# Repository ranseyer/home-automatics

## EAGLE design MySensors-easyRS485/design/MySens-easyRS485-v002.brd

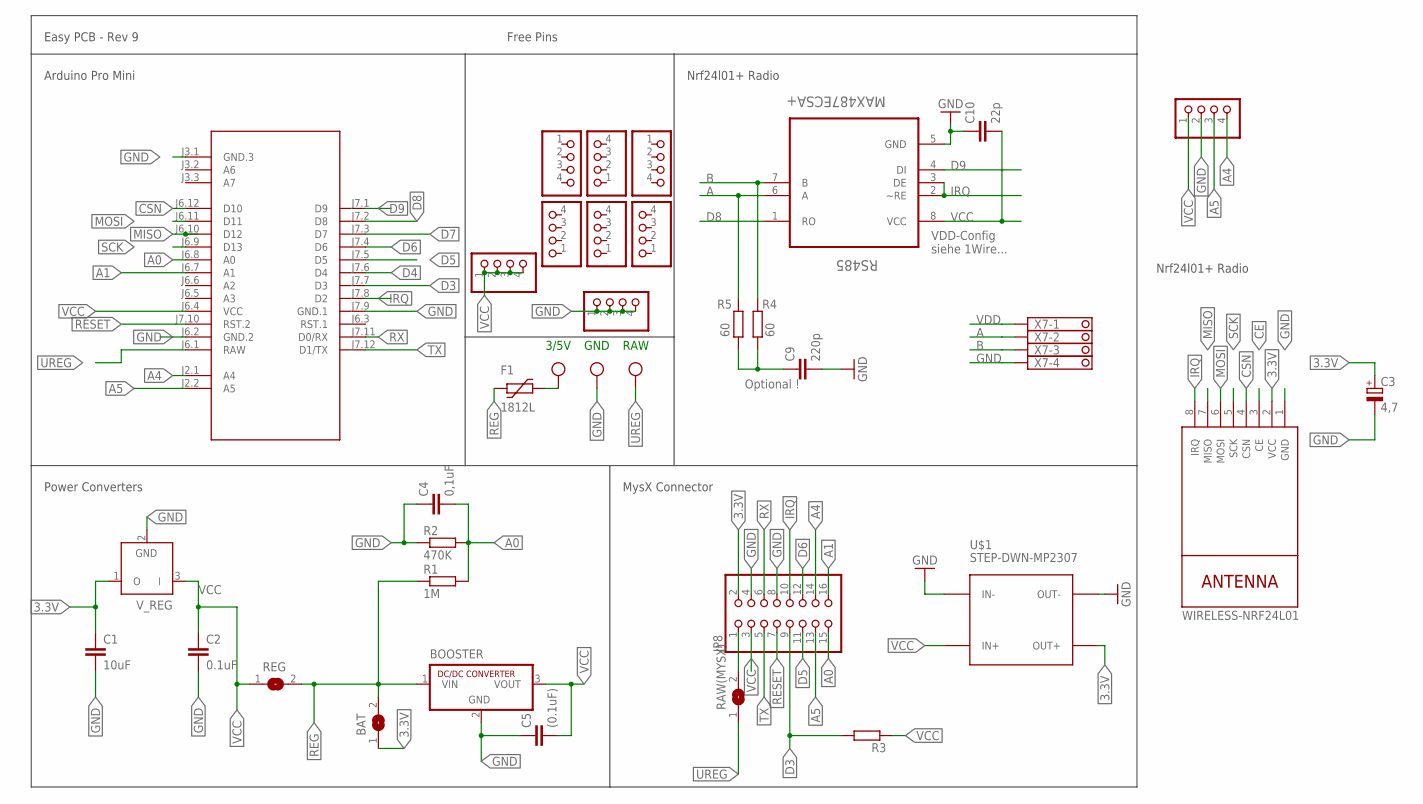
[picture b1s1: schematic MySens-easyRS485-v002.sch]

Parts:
.: W237-103
BAT: SJ
BOOSTER: R-78C1.8-1.0; SIP3
C1: 10uF; C1210
C2: 0.1uF; C1206
C3: 4,7; SMC_C
C4: 0,1uF; C1206
C5: (0.1uF); C1206
C9: 220p; C0805
C10: 22p; C0805
F1: 1812L
JP1, JP3, JP5, JP10, JP11, JP12, JP14, JP15, JP16: PINHD-1X04_2.54-S; 1X04-S
JP8: PINHD-2X08_2.54; 2X08
M1: ARDUINO-PRO-MINI-3.3V#NP; ARDUINO-PRO-MINI#NP
NRF24L01+: WIRELESS-NRF24L01
R1: 1M; R0805
R2: 470K; R0805
R3: R-EU_R0805; R0805
R4, R5: 60; R0805
RAW(MYSX): SJ
REG: SJ
RS485: MAX487ECSA+; SOIC127P600X175-8N
U$1: STEP-DWN-MP2307; DC-DC-STEP-DOWN-MP2307
V_REG: LP2950Z; TO92
X7: 1751264

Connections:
3.3V: BAT.1, C1.1, C3.+, JP8.2, NRF24L01+.2 (VCC), U$1.OUT+, V_REG.1 (O)
A: R5.2, RS485.6 (A), X7.2
A0: C4.2, JP8.15, M1.J6.8 (A0), R1.2, R2.2
A1: JP8.16, M1.J6.7 (A1)
A4: JP8.14, JP10.4, M1.J2.1 (A4)
A5: JP8.13, JP10.3, M1.J2.2 (A5)
B: R4.2, RS485.7 (B), X7.3
CE: NRF24L01+.3 (CE)
CSN: M1.J6.12 (D10), NRF24L01+.4 (CSN)
D3: JP8.9, M1.J7.7 (D3), R3.2
D4: M1.J7.6 (D4)
D5: JP8.11, M1.J7.5 (D5)
D6: JP8.12, M1.J7.4 (D6)
D7: M1.J7.3 (D7)
D8: M1.J7.2 (D8), RS485.1 (RO)
D9: M1.J7.1 (D9), RS485.4 (DI)
GND: ..2, BOOSTER.2 (GND), C1.2, C2.2, C3.-, C4.1, C5.1, C9.2, C10.1, JP1.1, JP1.2, JP1.3, JP1.4, JP8.4, JP8.8, JP10.2, M1.J3.1 (GND.3), M1.J6.2 (GND.2), M1.J7.9 (GND.1), NRF24L01+.1 (GND), R2.1, RS485.5 (GND), U$1.IN-, U$1.OUT-, V_REG.2 (GND), X7.4
IRQ: JP8.10, M1.J7.8 (D2), NRF24L01+.8 (IRQ), RS485.2 (~RE), RS485.3 (DE)
MISO: M1.J6.10 (D12), NRF24L01+.7 (MISO)
MOSI: M1.J6.11 (D11), NRF24L01+.6 (MOSI)
unnamed: JP8.1, RAW(MYSX).2
unnamed: ..3, F1.P$2 (2)
unnamed: C9.1, R4.1, R5.1
REG: BAT.2, BOOSTER.1 (VIN), F1.P$1 (1), R1.1, REG.2
RESET: JP8.7, M1.J7.10 (RST.2)
RX: JP8.6, M1.J7.11 (D0/RX)
SCK: M1.J6.9 (D13), NRF24L01+.5 (SCK)
TX: JP8.5, M1.J7.12 (D1/TX)
UREG: ..1, M1.J6.1 (RAW), RAW(MYSX).1
VCC: BOOSTER.3 (VOUT), C2.1, C5.2, C10.2, JP3.1, JP3.2, JP3.3, JP3.4, JP8.3, JP10.1, M1.J6.4 (VCC), R3.1, REG.1, RS485.8 (VCC), U$1.IN+, V_REG.3 (I)
VDD: X7.1

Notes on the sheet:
GND
3/5V
RAW
Easy PCB - Rev 9
Arduino Pro Mini
MysX Connector
Nrf24l01+ Radio
Power Converters
Free Pins
VDD-Config siehe 1Wire...
Optional !

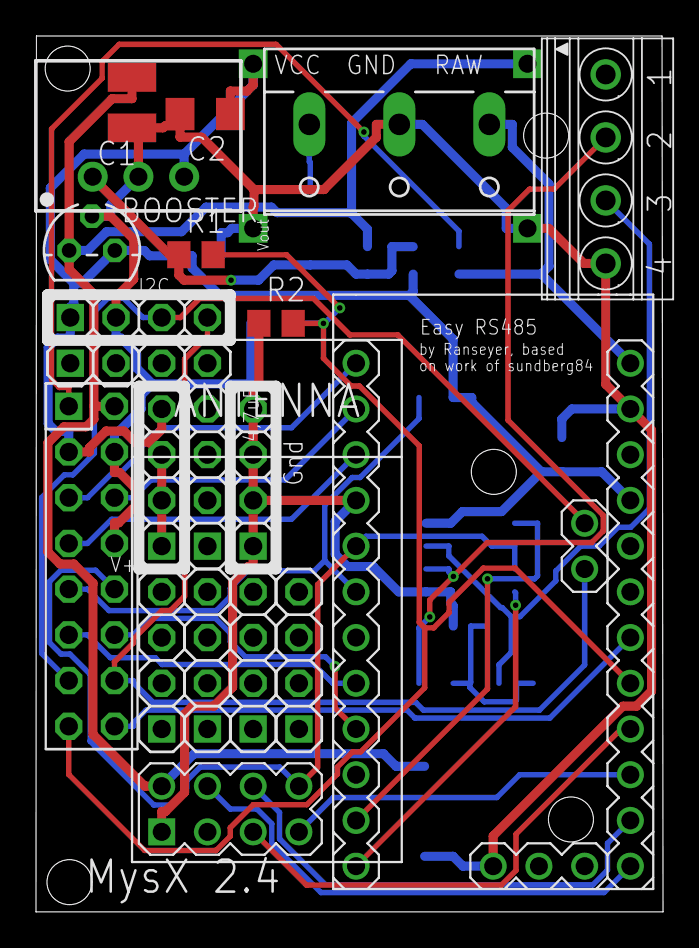
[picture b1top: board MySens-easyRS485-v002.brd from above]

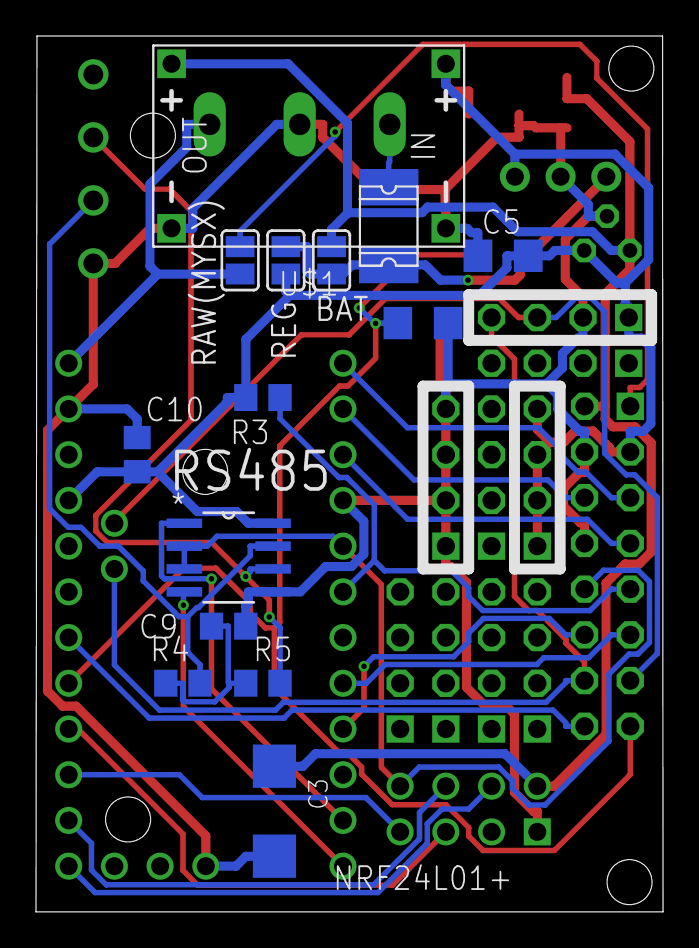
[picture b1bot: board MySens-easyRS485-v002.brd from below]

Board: 2 copper layers, 34.8 x 48.7 mm, 34 parts (14 on the bottom side), 27 nets.

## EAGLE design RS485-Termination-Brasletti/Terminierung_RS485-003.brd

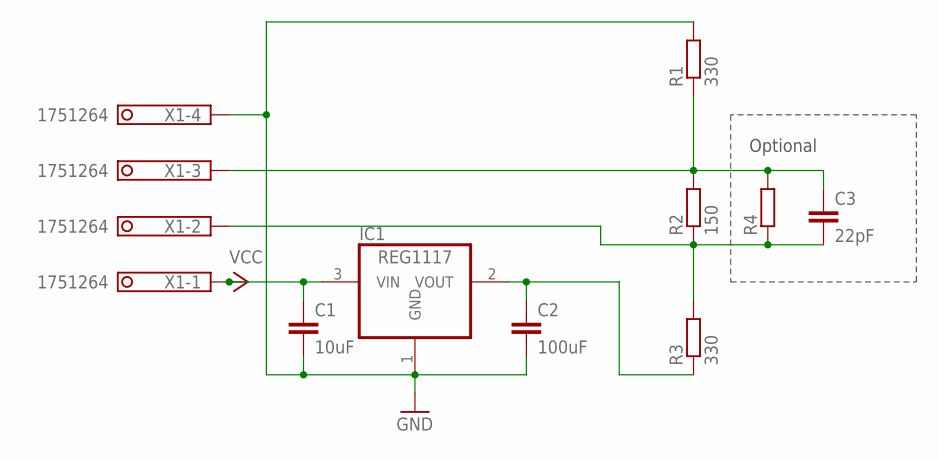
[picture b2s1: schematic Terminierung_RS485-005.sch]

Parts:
C1: 10uF; C0805K
C2: 100uF; C0805K
C3: 22pF; C0805K
IC1: REG1117; SOT223
R1, R3: 330; R0805
R2: 150; R0805
R4: R-EU_M1206; M1206
X1: 1751264

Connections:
GND: C1.2, C2.2, IC1.1 (GND), R1.2, X1.4
unnamed: C2.1, IC1.2 (VOUT), R3.1
unnamed: C3.1, R1.1, R2.2, R4.2, X1.3
unnamed: C3.2, R2.1, R3.2, R4.1, X1.2
VCC: C1.1, IC1.3 (VIN), X1.1

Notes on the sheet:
Optional

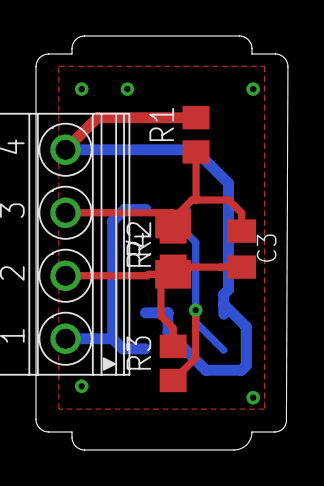
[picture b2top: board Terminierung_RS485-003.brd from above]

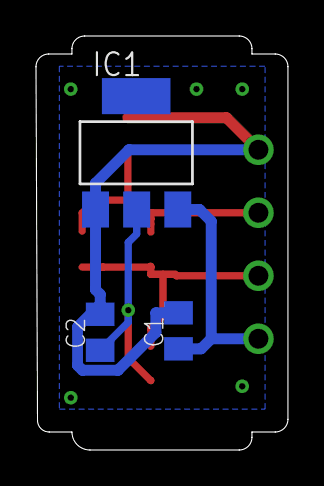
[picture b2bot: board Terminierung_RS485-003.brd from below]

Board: 2 copper layers, 14.0 x 23.0 mm, 9 parts (3 on the bottom side), 5 nets.

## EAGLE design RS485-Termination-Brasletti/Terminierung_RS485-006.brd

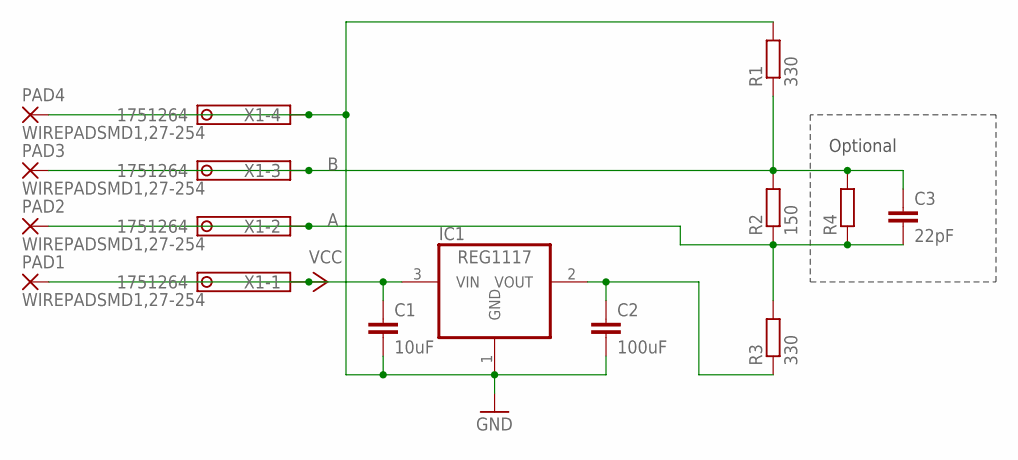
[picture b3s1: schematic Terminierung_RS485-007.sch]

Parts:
C1: 10uF; C0805K
C2: 100uF; C0805K
C3: 22pF; C0805K
IC1: REG1117; SOT223
PAD1, PAD2, PAD3, PAD4: WIREPADSMD1,27-254; SMD1,27-2,54
R1, R3: 330; R0805
R2: 150; R0805
R4: R-EU_M1206; M1206
X1: 1751264

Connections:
A: C3.2, PAD2.1, R2.1, R3.2, R4.1, X1.2
B: C3.1, PAD3.1, R1.1, R2.2, R4.2, X1.3
GND: C1.2, C2.2, IC1.1 (GND), PAD4.1, R1.2, X1.4
unnamed: C2.1, IC1.2 (VOUT), R3.1
VCC: C1.1, IC1.3 (VIN), PAD1.1, X1.1

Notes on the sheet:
Optional

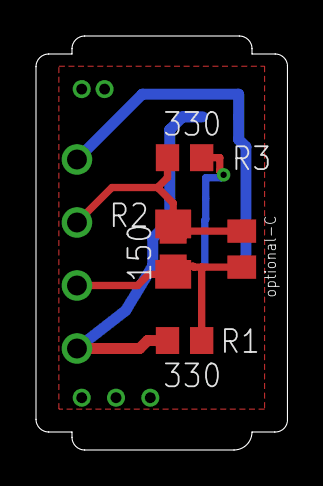
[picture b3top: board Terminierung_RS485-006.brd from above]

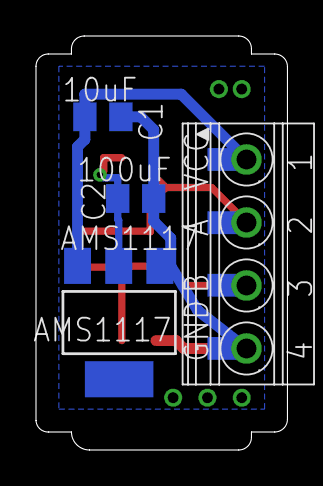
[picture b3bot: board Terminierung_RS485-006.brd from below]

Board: 2 copper layers, 14.0 x 23.0 mm, 13 parts (8 on the bottom side), 5 nets.

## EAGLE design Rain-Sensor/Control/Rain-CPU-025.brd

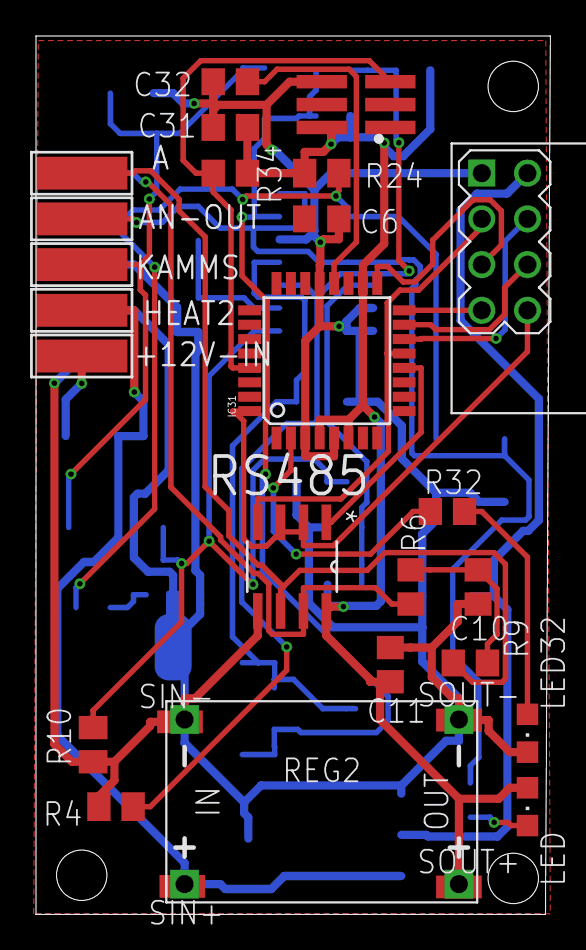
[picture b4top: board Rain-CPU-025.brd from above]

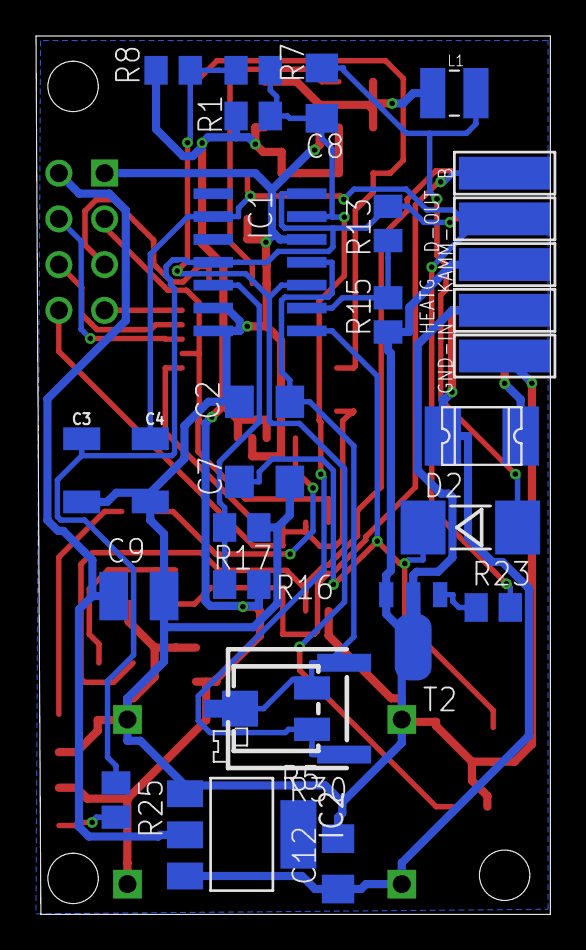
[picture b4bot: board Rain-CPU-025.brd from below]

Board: 2 copper layers, 28.6 x 48.8 mm, 57 parts (29 on the bottom side), 31 nets.

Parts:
+12V-IN: WIREPADSMD5-1,8; 5-1,8
A: WIREPADSMD5-1,8; 5-1,8
AN-OUT: WIREPADSMD5-1,8; 5-1,8
B: WIREPADSMD5-1,8; 5-1,8
C2: 20pF; C1206
C3, C4: 1,5uF; 1210
C6: 104; C0805
C7: 0,1µ; C1206
C8: 5pF; C1206
C9: 10uF; C1210
C10: 220p; C0805
C11: 22p; C0805
C12: 0.1uF; C1206
C31, C32: 100n; C0805
D2: MELF-MLL41
D-OUT: WIREPADSMD5-1,8; 5-1,8
F1: 1812L
GND-IN: WIREPADSMD5-1,8; 5-1,8
HEAT2: WIREPADSMD5-1,8; 5-1,8
HEATG: WIREPADSMD5-1,8; 5-1,8
IC1: LM339D; SO14
IC2: REG1117; SOT223
IC31: ATMEGA168-TQFP; TQFP32-08
KAMM-: WIREPADSMD5-1,8; 5-1,8
KAMMS: WIREPADSMD5-1,8; 5-1,8
L1: 1mH; WE-LQ_M
LED: lc-yellow; CHIPLED_0805
LED32: CHIPLED_0805
NRF24L01+: WIRELESS-NRF24L01
R1: 4K7; M0805
R4, R7, R8, R10: 100k; M0805
R5: RTRIM5X
R6, R9: 60; R0805
R13: 47k; M0805
R15: 10k; M0805
R16, R23, R24: 4k7; M0805
R17: 2k7; M0805
R25: 1k; M0805
R30: RTRIMTS63Z
R32: 1k; R0805
R34: R0805
REG2: Mini360; DC-DC-STEP-DOWN-MP2307
RS485: MAX487ECSA+; SOIC127P600X175-8N
SIN+: WIREPADSMD1,27-254; SMD1,27-2,54
SIN-: WIREPADSMD1,27-254; SMD1,27-2,54
SOUT+: WIREPADSMD1,27-254; SMD1,27-2,54
SOUT-: WIREPADSMD1,27-254; SMD1,27-2,54
T2: SOT89-BCE
X31: M03X2; 2X03-1.27MM_SMD

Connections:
3.3V: C9.1, IC2.2, NRF24L01+.2
-HEIZUNG_O.C.: HEATG.1, T2.C
A: A.1, R9.2, RS485.6
AN-OUT: AN-OUT.1, C3.1, IC1.4, IC1.14, R13.1, R25.1
B: B.1, R6.2, RS485.7
CE: IC31.13, NRF24L01+.3, RS485.4
CSN: IC31.14, NRF24L01+.4
D8: IC31.12, RS485.1
DIG-OUT: C4.1, D-OUT.1, IC1.2, R23.2, R24.2
GND: C2.1, C3.2, C4.2, C6.2, C7.2, C9.2, C10.2, C11.1, C12.2, C31.2, C32.2, GND-IN.1, IC1.6, IC1.7, IC1.12, IC2.1, IC31.3, IC31.5, IC31.21, KAMM-.1, L1.2, LED32.C, NRF24L01+.1, R4.2, R10.1, R15.1, R17.1, REG2.IN-, REG2.OUT-, RS485.5, SIN-.1, SOUT-.1, T2.E, X31.P$6
IN: +12V-IN.1, F1.P$2
IRQ: IC31.32, NRF24L01+.8, RS485.2, RS485.3
KAMMSENSOR: C8.2, D2.A, KAMMS.1, L1.1
M-RES: IC31.29, R34.2, X31.P$5
MISO: IC31.16, NRF24L01+.7
MOSI: IC31.15, NRF24L01+.6
unnamed: C10.1, R6.1, R9.1
unnamed: LED32.A, R32.2
unnamed: C8.1, IC1.13, R1.2, R5.1, R7.1, R30.1
unnamed: C32.1, IC31.20
unnamed: IC1.10, R4.1, R7.2, R8.1
unnamed: C2.2, IC1.11, R5.2, R5.3, R30.2, R30.3
unnamed: C7.1, D2.C, IC1.8, R10.2
unnamed: IC1.5, R16.1, R17.2
unnamed: R23.1, T2.B
unnamed: LED.C, R25.2
unnamed: IC1.9, R13.2, R15.2
RX_LED: IC31.2, R32.1
SCK: IC31.17, NRF24L01+.5
VCC: C11.2, C31.1, IC31.4, IC31.6, IC31.18, LED.A, R1.1, R8.2, R16.2, R24.1, R34.1, REG2.OUT+, RS485.8, SOUT+.1, X31.P$2
VIN: C12.1, F1.P$1, HEAT2.1, IC2.3, REG2.IN+, SIN+.1

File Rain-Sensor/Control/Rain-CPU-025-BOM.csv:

"Part";"Value";"Device";"Package";"Description";"MF";"MPN";"OC_FARNELL";"OC_NEWARK";"PACKAGE";"PROD_ID";"SUPPLIER";"VALUE";
"+12V-IN";"WIREPADSMD5-1,8";"WIREPADSMD5-1,8";"5-1,8";"Wire PAD connect wire on PCB";"";"";"";"";"";"";"";"";
"A";"WIREPADSMD5-1,8";"WIREPADSMD5-1,8";"5-1,8";"Wire PAD connect wire on PCB";"";"";"";"";"";"";"";"";
"AN-OUT";"WIREPADSMD5-1,8";"WIREPADSMD5-1,8";"5-1,8";"Wire PAD connect wire on PCB";"";"";"";"";"";"";"";"";
"B";"WIREPADSMD5-1,8";"WIREPADSMD5-1,8";"5-1,8";"Wire PAD connect wire on PCB";"";"";"";"";"";"";"";"";
"C2";"20pF";"C-EUC1206";"C1206";"CAPACITOR, European symbol";"";"";"";"";"";"";"";"";
"C3";"1,5uF";"10UF-1210-50V-20%";"1210";"10.0µF ceramic capacitors";"";"";"";"";"";"CAP-09824";"";"10uF";
"C4";"1,5uF";"10UF-1210-50V-20%";"1210";"10.0µF ceramic capacitors";"";"";"";"";"";"CAP-09824";"";"10uF";
"C6";"104";"C-EUC0805";"C0805";"CAPACITOR, European symbol";"";"";"";"";"";"";"";"";
"C7";"0,1µ";"C-EUC1206";"C1206";"CAPACITOR, European symbol";"";"";"";"";"";"";"";"";
"C8";"5pF";"C-EUC1206";"C1206";"CAPACITOR, European symbol";"";"";"";"";"";"";"";"";
"C9";"10uF";"C-EUC1210";"C1210";"CAPACITOR, European symbol";"";"";"";"";"";"";"";"";
"C10";"220p";"C-EUC0805";"C0805";"CAPACITOR, European symbol";"";"";"";"";"";"";"";"";
"C11";"22p";"C-EUC0805";"C0805";"CAPACITOR, European symbol";"";"";"";"";"";"";"";"";
"C12";"0.1uF";"C-EUC1206";"C1206";"CAPACITOR, European symbol";"";"";"";"";"";"";"";"";
"C31";"100n";"C-EUC0805";"C0805";"CAPACITOR, European symbol";"";"";"";"";"";"";"";"";
"C32";"100n";"C-EUC0805";"C0805";"CAPACITOR, European symbol";"";"";"";"";"";"";"";"";
"D-OUT";"WIREPADSMD5-1,8";"WIREPADSMD5-1,8";"5-1,8";"Wire PAD connect wire on PCB";"";"";"";"";"";"";"";"";
"D2";"";"DIODE-MELF-MLL41";"MELF-MLL41";"DIODE";"";"";"";"";"";"";"";"";
"F1";"1812L";"1812L";"1812L";"";"";"";"";"";"";"";"";"";
"GND-IN";"WIREPADSMD5-1,8";"WIREPADSMD5-1,8";"5-1,8";"Wire PAD connect wire on PCB";"";"";"";"";"";"";"";"";
"HEAT2";"WIREPADSMD5-1,8";"WIREPADSMD5-1,8";"5-1,8";"Wire PAD connect wire on PCB";"";"";"";"";"";"";"";"";
"HEATG";"WIREPADSMD5-1,8";"WIREPADSMD5-1,8";"5-1,8";"Wire PAD connect wire on PCB";"";"";"";"";"";"";"";"";
"IC1";"LM339D";"LM339D";"SO14";"Low Power Low Offset Voltage Quad Comparators";"";"";"";"";"";"";"";"";
"IC2";"REG1117";"REG1117";"SOT223";"800mA and 1A Low Dropout (LDO) Positive Regulator";"";"REG1117";"1097566";"14P6981";"";"";"";"";
"IC31";"ATMEGA168-TQFP";"ATMEGA168-TQFP";"TQFP32-08";"Atmel Atmega 168/328/328P";"";"";"";"";"";"";"";"";
"KAMM-";"WIREPADSMD5-1,8";"WIREPADSMD5-1,8";"5-1,8";"Wire PAD connect wire on PCB";"";"";"";"";"";"";"";"";
"KAMMS";"WIREPADSMD5-1,8";"WIREPADSMD5-1,8";"5-1,8";"Wire PAD connect wire on PCB";"";"";"";"";"";"";"";"";
"L1";"1mH";"WE-LQ_1210";"WE-LQ_M";"SMD Inductor";"";"";"";"";"";"";"";"";
"LED";"lc-yellow";"LEDCHIPLED_0805";"CHIPLED_0805";"LED";"";"";"";"";"";"";"";"";
"LED32";"";"LEDCHIPLED_0805";"CHIPLED_0805";"LED";"";"";"";"";"";"";"";"";
"NRF24L01+";"WIRELESS-NRF24L01";"WIRELESS-NRF24L01";"WIRELESS-NRF24L01";"2.4 GHz Wireless Module based on NRF24L01 chip";"";"";"";"";"";"";"";"";
"R1";"4K7";"R-EU_M0805";"M0805";"RESISTOR, European symbol";"";"";"";"";"";"";"";"";
"R4";"100k";"R-EU_M0805";"M0805";"RESISTOR, European symbol";"";"";"";"";"";"";"";"";
"R5";"";"R-TRIMM5X";"RTRIM5X";"Trimm resistor";"";"";"";"";"";"";"";"";
"R6";"60";"R-EU_R0805";"R0805";"RESISTOR, European symbol";"";"";"";"";"";"";"";"";
"R7";"100k";"R-EU_M0805";"M0805";"RESISTOR, European symbol";"";"";"";"";"";"";"";"";
"R8";"100k";"R-EU_M0805";"M0805";"RESISTOR, European symbol";"";"";"";"";"";"";"";"";
"R9";"60";"R-EU_R0805";"R0805";"RESISTOR, European symbol";"";"";"";"";"";"";"";"";
"R10";"100k";"R-EU_M0805";"M0805";"RESISTOR, European symbol";"";"";"";"";"";"";"";"";
"R13";"47k";"R-EU_M0805";"M0805";"RESISTOR, European symbol";"";"";"";"";"";"";"";"";
"R15";"10k";"R-EU_M0805";"M0805";"RESISTOR, European symbol";"";"";"";"";"";"";"";"";
"R16";"4k7";"R-EU_M0805";"M0805";"RESISTOR, European symbol";"";"";"";"";"";"";"";"";
"R17";"2k7";"R-EU_M0805";"M0805";"RESISTOR, European symbol";"";"";"";"";"";"";"";"";
"R23";"4k7";"R-EU_M0805";"M0805";"RESISTOR, European symbol";"";"";"";"";"";"";"";"";
"R24";"4k7";"R-EU_M0805";"M0805";"RESISTOR, European symbol";"";"";"";"";"";"";"";"";
"R25";"1k";"R-EU_M0805";"M0805";"RESISTOR, European symbol";"";"";"";"";"";"";"";"";
"R30";"";"R-TRIMMTS63Z";"RTRIMTS63Z";"Trimm resistor";"";"";"";"";"";"";"";"";
"R32";"1k";"R-EU_R0805";"R0805";"RESISTOR, European symbol";"";"";"";"";"";"";"";"";
"R34";"";"R-EU_R0805";"R0805";"RESISTOR, European symbol";"";"";"";"";"";"";"";"";
"REG2";"Mini360";"DC-DC-STEP-DOWN-MP2307";"DC-DC-STEP-DOWN-MP2307";"DC/DC Step-Down Regulator based on MP2307DN chip";"";"";"";"";"";"";"";"";
"RS485";"MAX487ECSA+";"MAX487ECSA+";"SOIC127P600X175-8N";"Low-Power, Slew-Rate-Limited RS-485/RS-422 Transceivers";"";"MAX487ECSA+";"9724532";"68K4803";"SOIC-8";"";"Maxim";"";
"SIN+";"WIREPADSMD1,27-254";"WIREPADSMD1,27-254";"SMD1,27-2,54";"Wire PAD connect wire on PCB";"";"";"";"";"";"";"";"";
"SIN-";"WIREPADSMD1,27-254";"WIREPADSMD1,27-254";"SMD1,27-2,54";"Wire PAD connect wire on PCB";"";"";"";"";"";"";"";"";
"SOUT+";"WIREPADSMD1,27-254";"WIREPADSMD1,27-254";"SMD1,27-2,54";"Wire PAD connect wire on PCB";"";"";"";"";"";"";"";"";
"SOUT-";"WIREPADSMD1,27-254";"WIREPADSMD1,27-254";"SMD1,27-2,54";"Wire PAD connect wire on PCB";"";"";"";"";"";"";"";"";
"T2";"";"BC868-NPN-SOT89-BCE";"SOT89-BCE";"NPN Transistror";"";"";"";"";"";"";"";"";
"X31";"M03X2";"M03X2";"2X03-1.27MM_SMD";"";"";"";"";"";"";"";"";"";

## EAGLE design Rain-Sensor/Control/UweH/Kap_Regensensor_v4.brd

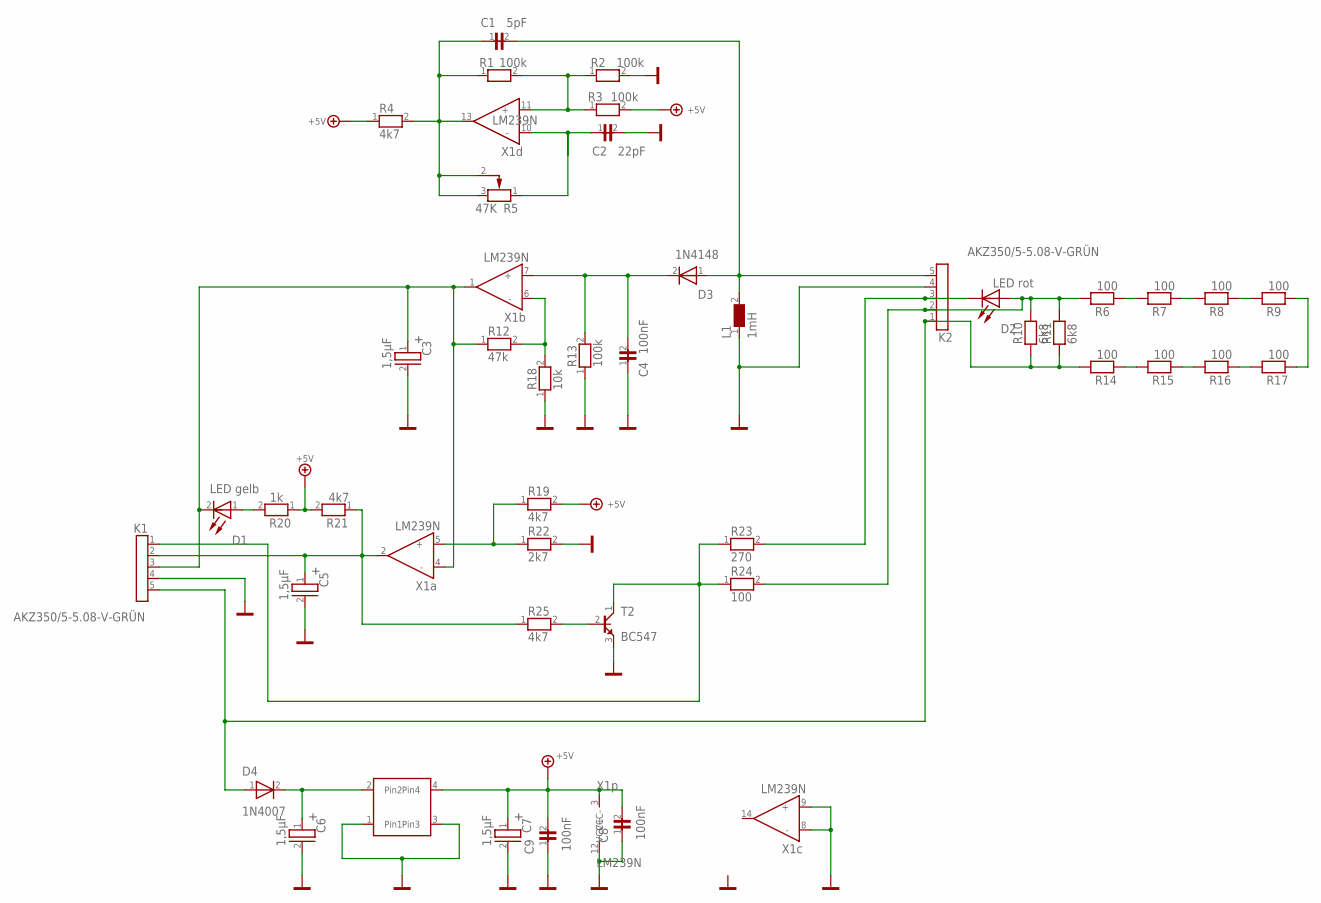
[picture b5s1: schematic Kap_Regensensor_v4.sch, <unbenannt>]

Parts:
C1: 5pF; 3X5R2,54_9
C2: 22pF; 3X5R2,54_12
C3: 1,5µF; D4R2,54_ELKO_23
C4: 100nF; 3X5R2,54_10
C5: 1,5µF; D4R2,54_ELKO_43
C6: 1,5µF; D4R2,54_ELKO_25
C7: 1,5µF; D4R2,54_ELKO_26
C8: 100nF; 3X5R2,54_52
C9: 100nF; 3X5R2,54_27
D1: LED gelb; LED_5MM_ROT_37
D3: 1N4148; DO35_11
D4: 1N4007; D_RM12,7_DM3_28
IC1: StepDown; StepDown_66
K1: AKZ350/5-5.08-V-GRÜN; Schraubklemme_5POLx5.08_22
K2: AKZ350/5-5.08-V-GRÜN; Schraubklemme_5POLx5.08_21
L1: 1mH; 5X8R5,08_29
R1: 100k; 0204_STEHEND_4
R2: 100k; 0204_5
R3: 100k; 0204_6
R4: 4k7; 0204_1
R5: 47K; TRIMMER_70WTD-K-P-C_7
R12: 47k; 0204_3
R13: 100k; 0204_STEHEND_8
R18: 10k; 0204_STEHEND_2
R19: 4k7; 0204_STEHEND_30
R20: 1k; 0204_36
R21: 4k7; 0204_STEHEND_35
R22: 2k7; 0204_STEHEND_31
R23: 270; 0204_STEHEND_33
R24: 100; 0204_STEHEND_34
R25: 4k7; 0204_32
T2: BC547; TO92_45
X1: LM239N; DIL14_0

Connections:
1: R1.2, R2.1, R3.1, X1.11 (+)
3: K2.3, R23.2
5: D4.1 (A), K1.5, K2.1
+: C4.2, D3.2 (K), R13.2, X1.7 (+)
+5V: C7.1 (+), C8.2, C9.2, IC1.4 (Pin4), R3.2, R4.1, R19.2, R20.1, R21.2, X1.3 (VCC+)
-: C2.1, R5.1 (A), X1.10 (-)
A: C1.1, R1.1, R4.2, R5.2 (S), R5.3 (E), X1.13 (OUT)
GND: C2.2, C3.2 (-), C4.1, C5.2 (-), C6.2 (-), C7.2 (-), C8.1, C9.1, IC1.1 (Pin1), IC1.3 (Pin3), K1.4, K2.4, L1.1, R2.2, R13.1, R18.1, R22.2, T2.3 (E), X1.8 (-), X1.9 (+), X1.12 (VCC-)
OUT: C3.1 (+), D1.2 (K), K1.3, R12.1, X1.1 (OUT), X1.4 (-)
Sig$8: R12.2, R18.2, X1.6 (-)
Sig$9: C1.2, D3.1 (A), K2.5, L1.2
Sig$10: C5.1 (+), K1.2, R21.1, R25.1, X1.2 (OUT)
Sig$11: D1.1 (A), R20.2
Sig$12: R19.1, R22.1, X1.5 (+)
Sig$13: R25.2, T2.2 (B)
Sig$14: K1.1, R23.1, R24.1, T2.1 (C)
Sig$16: C6.1 (+), D4.2 (K), IC1.2 (Pin2)
Sig$25: K2.2, R24.2

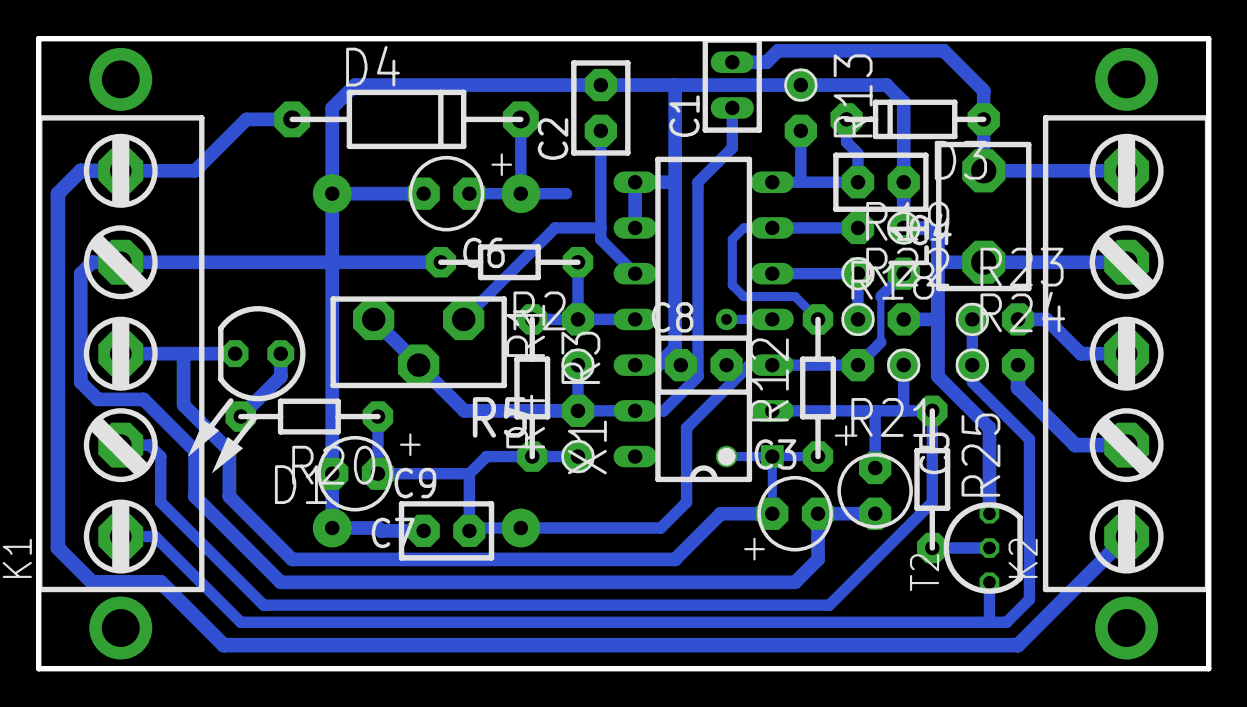
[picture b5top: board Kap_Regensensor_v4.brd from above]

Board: 2 copper layers, 65.0 x 35.0 mm, 33 parts (0 on the bottom side), 18 nets.

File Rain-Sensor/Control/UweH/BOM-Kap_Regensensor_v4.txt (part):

Stückliste exportiert aus D:/GitHub/home-automatics/Rain-Sensor/Control/UweH/Kap_Regensensor_v4.sch am 02.01.2018 15:19

Part Value                Device                          Package                    Description                                                                                                                                                                                                                                                                                                                                                                   
C1   5pF                  222268034478_9                  3X5R2,54_9                 Keramischer Rechteckkondensator                                                                                                                                                                                                                                                                                                                                               
C2   22pF                 222268034229_12                 3X5R2,54_12                Keramischer Rechteckkondensator                                                                                                                                                                                                                                                                                                                                               
C3   1,5µF                489D_25V_1,5µF_23               D4R2,54_ELKO_23            Tantalkondensatoren tropfenförmig, 489 D, Tantal-Elko 1,5uF  25V       , 489D155X0025B1V [1,5UF]                                                                                                                                                                                                                                                                              
C4   100nF                B37982-N5104-M_10               3X5R2,54_10                Bedrahtete Keramikkondensatoren, X7R/Z5U/Y5U, Kondensator  50V             , B37982-N5104-M [100NF]                                                                                                                                                                                                                                                                           
C5   1,5µF                489D_25V_1,5µF_43               D4R2,54_ELKO_43            Tantalkondensatoren tropfenförmig, 489 D, Tantal-Elko 1,5uF  25V       , 489D155X0025B1V [1,5UF]                                                                                                                                                                                                                                                                              
C6   1,5µF                489D_25V_1,5µF_25               D4R2,54_ELKO_25            Tantalkondensatoren tropfenförmig, 489 D, Tantal-Elko 1,5uF  25V       , 489D155X0025B1V [1,5UF]                                                                                                                                                                                                                                                                              
C7   1,5µF                489D_25V_1,5µF_26               D4R2,54_ELKO_26            Tantalkondensatoren tropfenförmig, 489 D, Tantal-Elko 1,5uF  25V       , 489D155X0025B1V [1,5UF]                                                                                                                                                                                                                                                                              
C8   100nF                B37982-N5104-M_52               3X5R2,54_52                Bedrahtete Keramikkondensatoren, X7R/Z5U/Y5U, Kondensator  50V             , B37982-N5104-M [100NF]                                                                                                                                                                                                                                                                           
C9   100nF                B37982-N5104-M_27               3X5R2,54_27                Bedrahtete Keramikkondensatoren, X7R/Z5U/Y5U, Kondensator  50V             , B37982-N5104-M [100NF]                                                                                                                                                                                                                                                                           
D1   LED gelb             LED_ROT_5MM_37                  LED_5MM_ROT_37             Leuchtdiode 5mm, Rot                                                                                                                                                                                                                                                                                                                                                          
D3   1N4148               1N4148_11                       DO35_11                    Universal-Diode  75V, 200mA, trr:4ns                                                                                                                                                                                                                                                                                                                                          
D4   1N4007               1N4007_28                       D_RM12,7_DM3_28            Universal-Diode 1000V, 1A                                                                                                                                                                                                                                                                                                                                                     
IC1  StepDown             STEPDOWN_66                     STEPDOWN_66                                                                                                                                                                                                                                                                                                                                                                                              
K1   AKZ350/5-5.08-V-GRÜN AKZ350/5-5.08-V-GRÜN_22         SCHRAUBKLEMME_5POLX5.08_22 Schraubklemme 5-polig RM5,08                                                                                                                                                                                                                                                                                                                                                  
K2   AKZ350/5-5.08-V-GRÜN AKZ350/5-5.08-V-GRÜN_21         SCHRAUBKLEMME_5POLX5.08_21 Schraubklemme 5-polig RM5,08                                                                                                                                                                                                                                                                                                                                                  
L1   1mH                  L-1MH_29                        5X8R5,08_29                DROSSEL 1MH Miniatur-Festinduktivitäten Anwendung: Entkopplung, Entzerrung bzw. Entstörung im HF/NF-Bereich und in selektiven Schaltungen. Ferritkern im Kunststoffgehäuse, radiale Anschlussdrähte im Raster 5 mm. Toleranz: ±5%. Zulässige Verlustleistung bei 40 °C/240 mW. Abm. 7,5 x 10,5 x 4,8 mm. Wert 1 mH ; Q bei 65 ; f MHz 0,6 ; R Ohm 14 ; I mA 130 ; Fres MHz 1, 
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

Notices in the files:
parts and their libraries:
diy-modules: Released under the Creative Commons Attribution 4.0 International License: http://creativecommons.org/licenses/by/4.0
SparkFun-Capacitors: Licensing: Creative Commons ShareAlike 4.0 International - https://creativecommons.org/licenses/by-sa/4.0
